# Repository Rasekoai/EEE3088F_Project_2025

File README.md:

## EEE3088F 2025 Micromouse Power Module Project

## Overview
This repository contains the design and implementation of the power subsystem for the Micro-mouse robot. The power subsystem is designed to efficiently manage power distribution to motors and provide USB connectivity for control interfaces.

## System Requirements

### Motor Control
- **Bidirectional operation** of up to 4 motors 
- **Motor specifications**:
  - 2x main brushed DC motors - 200mA max current draw at 15V battery
  - 2x auxiliary motors - 50mA each

### Battery Management
- **Battery**: 4.2V Lithium ion battery 
- **INA219** implementation for monitoring the battery on the I2C Bus
- **Charging**: Support for battery charging from the 5V input 
- **Dual charging modes**:
  - Higher charging current for battery (600mA)
  - Lower charging current for battery (100mA)

### USB Interface
- **Integrated USB-C port** for 5V output from the USB Host

### Power Control
- **ON/OFF switch**:
  - OFF state: Battery draw <50μA
  - ON state: Robot peak current is 1A
  - Switch turns on both 5V and 3V3

## Project Structure
This repository contains:
- Circuit schematic
- PCB design
- Datasheets for ICs used

## Assessment Information
This project is part of a group assignment. While the interim and final design reports are assessed as a group, individual contributions to the design sections will be evaluated separately.

## Contributors
- Rasekoai Mokose - student no: MKSRAS001
- Innocent Mkhonta - student no: SPHINN001

                                                                                                                                                                                                                                                                                                                                                                                                                                                                                                                                                                                                                                                                                                                                                                                                                                                                                                                                                                                                                                                                                                                                                                                                                                                                                                                                                                                                                                                                                                                                                                                                                                                                                                                                                                                                                                                                                                                                                                                                                                                                                                                                                                                                                                                                                                                                                                                                                                                                                                                                                                                                                                                                                                                                                                                                                                                                                                                                                                                                                                                                                                                                                                                                                                                                                                                                                                                                                                                                                                                                                                                                                                                                                                                                                                                                                                                                                                                                                                                                                                                                                                                                                                                                                                                                                                                                                                                                                                                                                                                                                                                                                                                                                                                                                                                                                                                                                                                                                                                                                                                                                                                                                                                                                                                                                                                                                                                                                                                                                                                                                                                                                                                                                                                                                                                                                                                                                                                                                                                                                                                                                                                                                                                                                                                                                                                                                                                                                                                                                                                                                                                                                                                                                                                                                                                                                                                                                                                                                                                                                                                                                                                                                                                                                                                                                                                                                                                                                                                                                                                                                                                                                                                                                                                                                                                                                                                                                                                                                                                                                                                                                                                                                                                                                                                                                                                                                                                                                                                                                                                                                                                                                                                                                                                                                                                                                                                                                                                                                                                                                                                                                                                                                                                                                                                                                                                                                                                                                                                                                                                                                                                                                                                                                                                                                                                                                                                                                                                                                                                                                                                                                                                                                                                                                                                                                                                                                                                                                                                                                                                                                                                                                                                                                                                                                                                                                                                                                                                                                                                                                                                                                                                                                                                                                                                                                                                                                                                                                                                                                                                                                                                                                                                                                                                                                                                                                                                                                                                                                                                                                                                                                                                                                                                                                                                                                                                                                                                                                                                                                                                                                                                                                                                                                                                                                                                                                                                                                                                                                                                                                                                                                                                                                                                                                                                                                                                                                                                                                                                                                                                                                                                                                                                                                                                                                                                                                                                                                                                                                                                                                                                                                                                                                                                                                                                                                                                                                                                                                                                                                                                                                                                                                                                                                                                                                                                                                                                                                                                                                                                                                                                                                                                                                                                                                                                                                                                                                                                                                                                                                                                                                                                                                                                                                                                                                                                                                                                                                                                                                                                                                                                                                                                                                                                                                                                                                                                                                                                                                                                                                                                                                                                                                                                                                                                                                                                                                                                                                                                                                                                                                                                                                                                                                                                                                                                                                                                                                                                                                                                                                                                                                                                                                                                                                                                                                                                                                                                                                                                                                                                                                                                                                                                                                                                                                                                                                                                                                                                                                                                                                                                                                                                                                                                                                                                                                                                                                                                                                                                                                                                                                                                                                                                                                                                                                                                                                                                                                                                                                                                                                                                                                                                                                                                                                                                                                                                                                                                                                                                                                                                                                                                                                                                                                                                                                                                                                                                                                                                                                                                                                                                                                                                                                                                                                                                                                                                                                                                                                                                                                                                                                                                                                                                                                                                                                                                                                                                                                                                                                                                                                                                                                                                                                                                                                                                                                                                                                                                                                                                                                                                                                                                                                                                                                                                                                                                                                                                                                                                                                                                                                                                                                                                                                                                                                                                                                                                                                                                                                                                                                                                                                                                                                                                                                                                                                                                                                                                                                                                                                                                                                                                                                                                                                                                                                                                                                                                                                                                                                                                                                                                                                                                                                                                                                                                                                                                                                                                                                                                                                                                                                                                                                                                                                                                                                                                                                                                                                                                                                                                                                                                                                                                                                                                                                                                                                                                                                                                                                                                                                                                                                                                                                                                                                                                                                                                                                                                                                                                                                                                                                                                                                                                                                                                                                                                                                                                                                                                                                                                                                                                                                                                                                                                                                                                                                                                                                                                                                                                                                                                                                                                                                                                                                                                                                                                                                                                                                                                                                                                                                                                                                                                                                                                                                                                                                                                                                                                                                                                                                                                                                                                                                                                                                                                                                                                                                                                                                                                                                                                                                                                                                                                                                                                                                                                                                                                                                                                                                                                                                                                                                                                                                                                                                                                                                                                                                                                                                                                                                                                                                                                                                                                                                                                                                                                                                                                                                                                                                                                                                                                                                                                                                                                                                                                                                                                                                                                                                                                                                                                                                                                                                                                                                                                                                                                                                                                                                                                                                                                                                                                                                                                                                                                                                                                                                                                                                                                                                                                                                                                                                                                                                                                                                                                                                                                                                                                                                                                                                                                                                                                                                                                                                                                                                                                                                                                                                                                                                                                                                                                                                                                                                                                                                                                                                                                                                                                                                                                                                                                                                                                                                                                                                                                                                                                                                                                                                                                                                                                                                                                                                                                                                                                                                                                                                                                                                                                                                                                                                                                                                                                                                                                                                                                                                                                                                                                                                                                                                                                                                                                                                                                                                                                                                                                                                                                                                                                                                                                                                                                                                                                                                                                                                                                                                                                                                                                                                                                                                                                                                                                                                                                                                                                                                                                                                                                                                                                                                                                                                                                                                                                                                                                                                                                                                                                                                                                                                                                                                                                                                                                                                                                                                                                                                                                                                                                                                                                                                                                                                                                                                                                                                                                                                                                                                                                                                                                                                                                                                                                                                                                                                                                                                                                                                                                                                                                                                                                                                                                                                                                                                                                                                                                                                                                                                                                                                                                                                                                                                                                                                                                                                                                                                                                                                                                                                                                                                                                                                                                                                                                                                                                                                                                                                                                                                                                                                                                                                                                                                                                                                                                                                                                                                                                                                                                                                                                                                                                                                                                                                                                                                                                                                                                                                                                                                                                                                                                                                                                                                                                                                                                                                                                                                                                                                                                                                                                                                                                                                                                                                                                                                                                                                                                                                                                                                                                                                                                                                                                                                                                                                                                                                                                                                                                                                                                                                                                                                                                                                                                                                                                                                                                                                                                                                                                                                                                                                                                                                                                                                                                                                                                                                                                                                                                                                                                                                                                                                                                                                                                                                                                                                                                                                                                                                                                                                                                                                                                                                                                                                                                                                                                                                                                                                                                                                                                                                                                                                                                                                                                                                                                                                                                                                                                                                                                                                                                                                                                                                                                                                                                                                                                                                                                                                                                                                                                                                                                                                                                                                                                                                                                                                                                                                                                                                                                                                                                                                                                                                                                                                                                                                                                                                                                                                                                                                                                                                                                                                                                                                                                                                                                                                                                                                                                                                                                                                                                                                                                                                                                                                                                                                                                                                                                                                                                                                                                                                                                                                                                                                                                                                                                                                                                                                                                                                                                                                                                                                                                                                                                                                                                                                                                                                                                                                                                                                                                                                                                                                                                                                                                                                                                                                                                                                                                                                                                                                                                                                                                                                                                                                                                                                                                                                                                                                                                                                                                                                                                                                                                                                                                                                                                                                                                                                                                                                                                                                                                                                                                                                                                                                                                                                                                                                                                                                                                                                                                                                                                                                                                                                                                                                                                                                                                                                                                                                                                                                                                                                                                                                                                                                                                                                                                                                                                                                                                                                                                                                                                                                                                                                                                                                                                                                                                                                                                                                                                                                                                                                                                                                                                                                                                                                                                                                                                                                                                                                                                                                                                                                                                                                                                                                                                                                                                                                                                                                                                                                                                                                                                                                                                                                                                                                                                                                                                                                                                                                                                                                                                                                                                                                                                                                                                                                                                                                                                                                                                                                                                                                                                                                                                                                                                                                                                                                                                                                                                                                                                                                                                                                                                                                                                                                                                                                                                                                                                                                                                                                                                                                                                                                                                                                                                                                                                                                                                                                                                                                                                                                                                                                                                                                                                                                                                                                                                                                                                                                                                                                                                                                                                                                                                                                                                                                                                                                                                                                                                                                                                                                                                                                                                                                                                                                                                                                                                                                                                                                                                                                                                                                                                                                                                                                                                                                                                                                                                                                                                                                                                                                                                                                                                                                                                                                                                                                                                                                                                                                                                                                                                                                                                                                                                                                                                                                                                                                                                                                                                                                                                                                                                                                                                                                                                                                                                                                                                                                                                                                                                                                                                                                                                                                                                                                                                                                                                                                                                                                                                                                                                                                                                                                                                                                                                                                                                                                                                                                                                                                                                                                                                                                                                                                                                                                                                                                                                                                                                                                                                                                                                                                                                                                                                                                                                                                                                                                                                                                                                                                                                                                                                                                                                                                                                                                                                                                                                                                                                                                                                                                                                                                                                                                                                                                                                                                                                                                                                                                                                                                                                                                                                                                                                                                                                                                                                                                                                                                                                                                                                                                                                                                                                                                                                                                                                                                                                                                                                                                                                                                                                                                                                                                                                                                                                                                                                                                                                                                                                                                                                                                                                                                                                                                                                                                                                                                                                                                                                                                                                                                                                                                                                                                                                                                                                                                                                                                                                                                                                                                                                                                                                                                                                                                                                                                                                                                                                                                                                                                                                                                                                                                                                                                                                                                                                                                                                                                                                                                                                                                                                                                                                                                                                                                                                                                                                                                                                                                                                                                                                                                                                                                                                                                                                                                                                                                                                                                                                                                                                                                                                                                                                                                                                                                                                                                                                                                                                                                                                                                                                                                                                                                                                                                                                                                                                                                                                                                                                                                                                                                                                                                                                                                                                                                                                                                                                                                                                                                                                                                                                                                                                                                                                                                                                                                                                                                                                                                                                                                                                                                                                                                                                                                                                                                                                                                                                                                                                                                                                                                                                                                                                                                                                                                                                                                                                                                                                                                                                                                                                                                                                                                                                                                                                                                                                                                                                                                                                                                                                                                                                                                                                                                                                                                                                                                                                                                                                                                                                                                                                                                                                                                                                                                                                                                                                                                                                                                                                                                                                                                                                                                                                                                                                                                                                                                                                                                                                                                                                                                                                                                                                                                                                                                                                                                                                                                                                                                                                                                                                                                                                                                                                                                                                                                                                                                                                                                                                                                                                                                                                                                                                                                                                                                                                                                                                                                                                                                                                                                                                                                                                                                                                                                                                                                                                                                                                                                                                                                                                                                                                                                                                                                                                                                                                                                                                                                                                                                                                                                                                                                                                                                                                                                                                                                                                                                                                                                                                                                                                                                                                                                                                                                                                                                                                                                                                                                                                                                                                                                                                                                                                                                                                                                                                                                                                                                                                                                                                                                                     -

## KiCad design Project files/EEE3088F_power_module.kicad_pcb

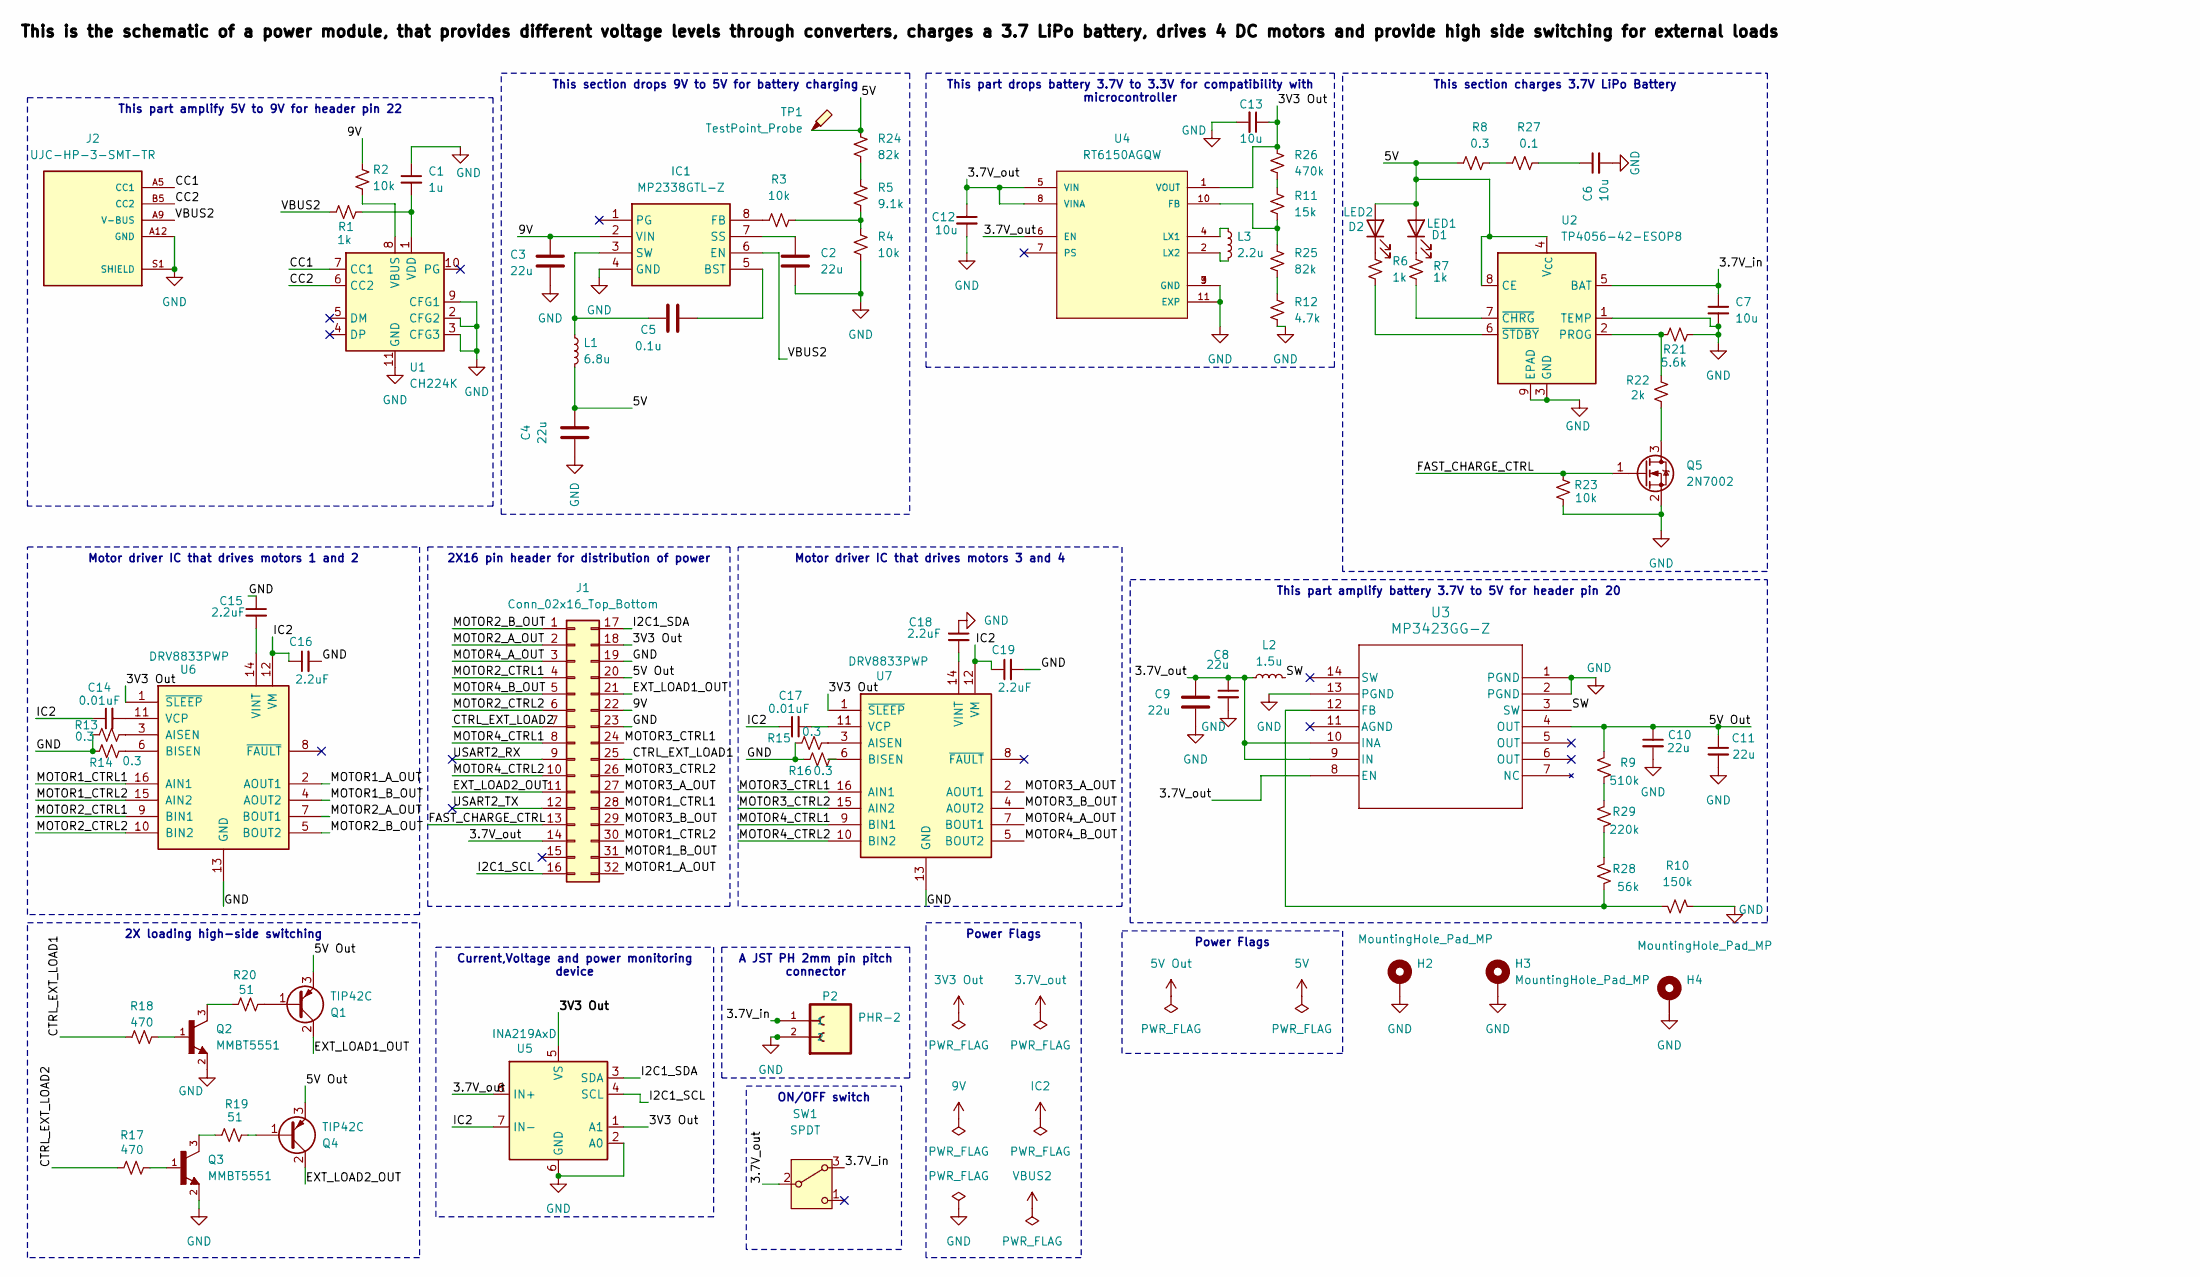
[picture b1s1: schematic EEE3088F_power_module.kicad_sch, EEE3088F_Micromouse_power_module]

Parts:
C1: 1u; C_0402_1005Metric
C2, C3, C4, C8, C9, C10, C11: 22u; C_1206_3216Metric
C5: 0.1u; C_0603_1608Metric
C6, C7, C12, C13: 10u; C_0805_2012Metric
C14, C17: 0.01uF; C_0805_2012Metric
C15, C16, C18, C19: 2.2uF; C_1206_3216Metric
H2, H3, H4: MountingHole_Pad_MP; MountingHole_2.2mm_M2_ISO7380_Pad
IC1: MP2338GTL-Z; MP2338GTLZ; Mouser Part Number 946-MP2338GTL-Z
J1: Conn_02x16_Top_Bottom; PinHeader_2x16_P2.54mm_Vertical
J2: UJC-HP-3-SMT-TR; CUI_UJC-HP-3-SMT-TR; PARTREV 04/30/2020
L1: 6.8u; L_1008_2520Metric
L2: 1.5u; L_0805_2012Metric
L3: 2.2u; L_1210_3225Metric
LED1: D1; LED_0805_2012Metric
LED2: D2; LED_0805_2012Metric
P2: PHR-2; JST_PHR-2
Q1, Q4: TIP42C; TO-220-3_Vertical
Q2, Q3: MMBT5551; SOT23-3; DigiKey_Part_Number 2156-MMBT5551-ND
Q5: 2N7002; SOT-23
R1, R6, R7: 1k; R_0805_2012Metric
R2, R3, R4, R23: 10k; R_0805_2012Metric
R5: 9.1k; R_0603_1608Metric
R8, R13, R14, R15, R16: 0.3; R_0805_2012Metric
R9: 510k; R_0603_1608Metric
R10: 150k; R_0805_2012Metric
R11: 15k; R_0805_2012Metric
R12: 4.7k; R_0805_2012Metric
R17, R18: 470; R_0805_2012Metric
R19, R20: 51; R_0805_2012Metric
R21: 5.6k; R_0805_2012Metric
R22: 2k; R_0805_2012Metric
R24: 82k; R_0805_2012Metric
R25: 82k; R_0603_1608Metric
R26: 470k; R_0805_2012Metric
R27: 0.1; R_1206_3216Metric
R28: 56k; R_0603_1608Metric
R29: 220k; R_0603_1608Metric
SW1: SPDT; NEWSWITCH
TP1: TestPoint_Probe; TestPoint_2mm
U1: CH224K; SSOP-10-1EP_3.9x4.9mm_P1mm_EP2.1x3.3mm
U2: TP4056-42-ESOP8; SOIC-8-1EP_3.9x4.9mm_P1.27mm_EP2.41x3.3mm_ThermalVias
U3: MP3423GG-Z; QFN14_MP3423_MNP
U4: RT6150AGQW; SON50P300X300X80-11N
U5: INA219AxD; SOIC-8_3.9x4.9mm_P1.27mm
U6, U7: DRV8833PWP; HTSSOP-16-1EP_4.4x5mm_P0.65mm_EP3.4x5mm_Mask2.46x2.31mm_The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

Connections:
3.7V_in: C7.1, P2.1, SW1.3 (A), U2.5 (BAT)
3.7V_out: C8.1, C9.1, C12.1, J1.14, L2.2, SW1.2 (B), U3.8 (EN), U3.9 (IN), U3.10 (INA), U4.5 (VIN), U4.6 (EN), U4.8 (VINA), U5.8 (IN+)
3V3 Out: C13.1, J1.18, R26.1, U4.1 (VOUT), U5.1 (A1), U5.5 (VS), U6.1 (~SLEEP), U7.1 (~SLEEP)
5V: C4.2, L1.2, LED1.2 (A), LED2.2 (A), R8.2, R24.1, TP1.1, U2.4 (V_{CC}), U2.8 (CE)
5V Out: C10.1, C11.1, J1.20, Q1.3 (E), Q4.3 (E), R9.2, U3.4 (OUT)
9V: C3.1, IC1.2 (VIN), J1.22, R2.1
/CC1: J2.A5 (CC1), U1.7 (CC1)
/CC2: J2.B5 (CC2), U1.6 (CC2)
/CTRL_EXT_LOAD1: J1.25, R18.1
/CTRL_EXT_LOAD2: J1.7, R17.1
/EXT_LOAD1_OUT: J1.21, Q1.2 (C)
/EXT_LOAD2_OUT: J1.11, Q4.2 (C)
/FAST_CHARGE_CTRL: J1.13, Q5.1 (G), R23.2
/I2C1_SCL: J1.16, U5.4 (SCL)
/I2C1_SDA: J1.17, U5.3 (SDA)
/MOTOR1_A_OUT: J1.32, U6.2 (AOUT1)
/MOTOR1_B_OUT: J1.31, U6.4 (AOUT2)
/MOTOR1_CTRL1: J1.28, U6.16 (AIN1)
/MOTOR1_CTRL2: J1.30, U6.15 (AIN2)
/MOTOR2_A_OUT: J1.2, U6.7 (BOUT1)
/MOTOR2_B_OUT: J1.1, U6.5 (BOUT2)
/MOTOR2_CTRL1: J1.4, U6.9 (BIN1)
/MOTOR2_CTRL2: J1.6, U6.10 (BIN2)
/MOTOR3_A_OUT: J1.27, U7.2 (AOUT1)
/MOTOR3_B_OUT: J1.29, U7.4 (AOUT2)
/MOTOR3_CTRL1: J1.24, U7.16 (AIN1)
/MOTOR3_CTRL2: J1.26, U7.15 (AIN2)
/MOTOR4_A_OUT: J1.3, U7.7 (BOUT1)
/MOTOR4_B_OUT: J1.5, U7.5 (BOUT2)
/MOTOR4_CTRL1: J1.8, U7.9 (BIN1)
/MOTOR4_CTRL2: J1.10, U7.10 (BIN2)
/RESV: J1.15
/USART2_RX: J1.9
/USART2_TX: J1.12
GND: C1.1, C2.2, C3.2, C4.1, C6.2, C7.2, C8.2, C9.2, C10.2, C11.2, C12.2, C13.2, C15.1, C16.2, C18.1, C19.2, H2.MP, H3.MP, H4.MP, IC1.4 (GND), J1.19, J1.23, J2.A12 (GND), J2.S1 (SHIELD), P2.2, Q2.2, Q3.2, Q5.2 (S), R4.2, R10.2, R12.2, R13.1, R14.1, R15.1, R16.1, R21.2, R23.1, U1.2 (CFG2), U1.3 (CFG3), U1.9 (CFG1), U1.11 (GND), U2.1 (TEMP), U2.3 (GND), U2.9 (EPAD), U3.1 (PGND), U3.2 (PGND), U3.13 (PGND), U4.3 (GND), U4.9 (GND), U4.11 (EXP), U5.2 (A0), U5.6 (GND), U6.13 (GND), U6.17 (GND), U7.13 (GND), U7.17 (GND)
IC2: C14.1, C16.1, C17.1, C19.1, U5.7 (IN-), U6.12 (VM), U7.12 (VM)
unnamed: C6.1, R27.1
unnamed: C5.2, IC1.5 (BST)
unnamed: IC1.8 (FB), R3.1
unnamed: C2.1, IC1.7 (SS)
unnamed: C5.1, IC1.3 (SW), L1.1
unnamed: L2.1, U3.3 (SW), U3.14 (SW)
unnamed: LED1.1 (K), R7.1
unnamed: LED2.1 (K), R6.1
unnamed: Q1.1 (B), R20.2
unnamed: Q2.1, R18.2
unnamed: Q2.3, R20.1
unnamed: Q3.1, R17.2
unnamed: Q3.3, R19.1
unnamed: Q4.1 (B), R19.2
unnamed: Q5.3 (D), R22.2
unnamed: R3.2, R4.1, R5.2
unnamed: R11.1, R26.2
unnamed: R12.1, R25.2
unnamed: R5.1, R24.2
unnamed: R8.1, R27.2
unnamed: R28.2, R29.1
unnamed: R9.1, R29.2
unnamed: R2.2, U1.8 (VBUS)
unnamed: C1.2, R1.2, U1.1 (VDD)
unnamed: R21.1, R22.1, U2.2 (PROG)
unnamed: R7.2, U2.7 (~CHRG)
unnamed: R6.2, U2.6 (~STDBY)
unnamed: R10.1, R28.1, U3.12 (FB)
unnamed: R11.2, R25.1, U4.10 (FB)
unnamed: L3.1, U4.4 (LX1)
unnamed: L3.2, U4.2 (LX2)
unnamed: R13.2, U6.3 (AISEN)
unnamed: R14.2, U6.6 (BISEN)
unnamed: C14.2, U6.11 (VCP)
unnamed: C15.2, U6.14 (VINT)
unnamed: R15.2, U7.3 (AISEN)
unnamed: R16.2, U7.6 (BISEN)
unnamed: C17.2, U7.11 (VCP)
unnamed: C18.2, U7.14 (VINT)
VBUS2: IC1.6 (EN), J2.A9 (V-BUS), R1.1

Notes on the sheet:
Power Flags
This section charges 3.7V LiPo Battery
Motor driver IC that drives motors 3 and 4
This part amplify 5V to 9V for header pin 22
2X16 pin header for distribution of power
Motor driver IC that drives motors 1 and 2
ON/OFF switch
A JST PH 2mm pin pitch connector
Current,Voltage and power monitoring device
This part drops battery 3.7V to 3.3V for compatibility with microcontroller
Power Flags
This part amplify battery 3.7V to 5V for header pin 20
This section drops 9V to 5V for battery charging
2X loading high-side switching

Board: 2 copper layers, 74 parts (1 on the bottom side), 73 nets, no tracks yet.

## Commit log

2025-03-11 added a motor driver l298 datasheeet
2025-03-11 added a battery charging ic datasheeet
2025-03-21 added a TB6612 ic datasheeet
2025-03-21 added the datasheet for DRV8833
2025-05-31 these are the files for the project
2025-05-31 i have added a more detailed description of this project
2025-05-31 moved files into folders to make the repo neat
2025-05-31 added a real PCB picture to the repo
